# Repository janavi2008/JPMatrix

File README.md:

# JPMatrix
a scalable led matrix display where 'tiles' can connect to each other in a row to allow for any size display. each tile has a 8x8 matrix. it runs on a rapberry pi pico that has to be connected externally, with shift registers for multiplexing, and a logic level shifter ic to convert the 3.3v pico outputs to 5v for the shift register inputs.
im writing the firmware to display conways game of life, because i think itd look super cool.

# How it works
multiplexing is a way to control a bunch of leds using fewer pins on the microcontroller. basically, instead of connecting each led to its own output pin, the leds are arranged in a matrix, and all anodes in one column are tied together, and the cathodes in one row are tied together. each row and column is connected to a microcontroller pin. the microcontroller passes current through one row at a time and simultaneously connecting the columns with whichever leds are supposed to be on for that row. it cycles through the rows super fast, way faster for the human eye to comprehend, so it looks as if the leds are all lit up at the same time, when in reality, only one row is on at a time- this is known as persitance of vision. however, this still would use one output pin for each row and column (so 16 per tile) and thats not feasable, which is why im using shift registers.
shift registers let you transmit the data serially over one data line rather than one for each row and column, drastically saving the pin count. it used 4 pins - data, latch, clock, and oe(output enable). the data pin sends the data to the shift registers, the clock pin handles the timing(when to read the data pin), latch saves the data once its been loaded, and the oe manages when the data is outputted to the leds. multiple shift registers can be used by daisy chaining without needing more pins - each chip has a data in and a data out, so the data out from one chip can connect to the data in to another. im using one shift register for columns, and one for the rows. the one for the rows is a power shift register, with internal mosfets on each line, so it can handle higher currents.

# Design
i desinged a pcb, using IC 74HCT595 as a shift register, TPIC6C595 as a power shift register, 74HCT125 for logic level shifting, 64 LEDs, and input header pins to connect to the previous tile or the raspberry pi and output header pins to connect to the next tile. i also put in some resistors and decoupling capacitors.

# BOM

| Item | Qty | Supplier | Total Cost |
| :--- | :---: | :--- | ---: |
| raspberry pi pico | 1 | robu | $4.05 |
| TPIC6C595 | 2 | robu | $3.10 |
| 74HCT595 | 2 | robu | $1.00 |
| 74HCT125 | 2 | robu | $0.78 |
| 0805 smd LED | 128 | robu | $1.4 |
| 0603 smd 0.1uf capacitor | 6 | robu | $0.15 |
| 0603 smd 100uf electrolytic capacitor | 2 | robu | $0.22 |
| 0603 330 ohm resistor | 16 | robu | $0.15 |
| 0603 10k resistor | 2 | robu | $0.15 |
| 0603 100 ohm resistor | 2 | robu | $0.15 |
| male header pins | 16 | robu | $0.2 |
| pcb manufacture | 5 | zbotic | $10.00 |

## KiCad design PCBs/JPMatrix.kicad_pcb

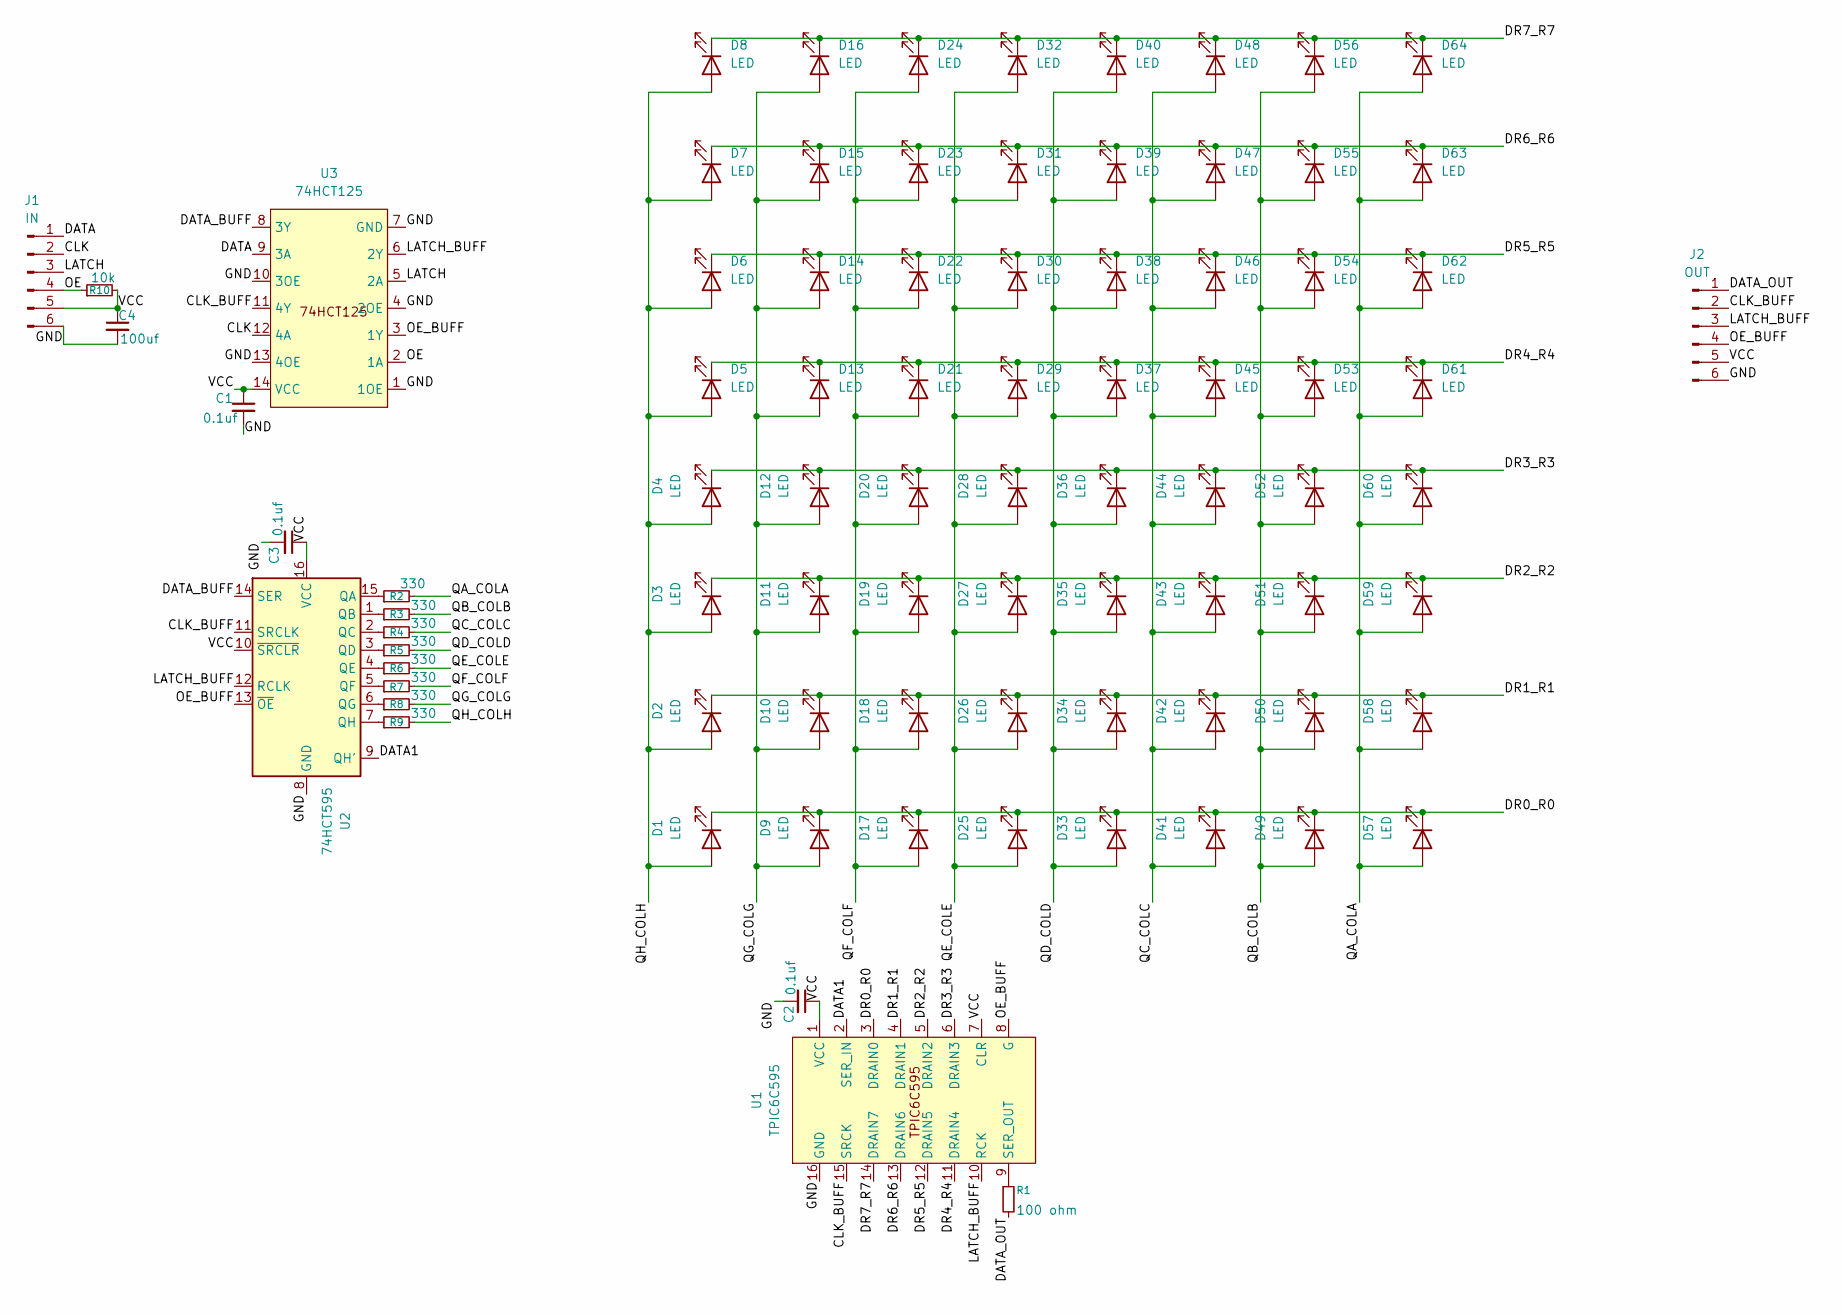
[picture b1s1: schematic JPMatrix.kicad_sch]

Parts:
C1, C2, C3: 0.1uf; C_0603_1608Metric_Pad1.08x0.95mm_HandSolder
C4: 100uf; CP_Elec_6.3x5.9
D1, D2, D3, D4, D5, D6, D7, D8, D9, D10, D11, D12, D13, D14, D15, D16, D17, D18, D19, D20, D21, D22, D23, D24, D25, D26, D27, D28, D29, D30, D31, D32, D33, D34, D35, D36, D37, D38, D39, D40, D41, D42, D43, D44, D45, D46, D47, D48, D49, D50, D51, D52, D53, D54, D55, D56, D57, D58, D59, D60, D61, D62, D63, D64: LED; LED_0805_2012Metric_Pad1.15x1.40mm_HandSolder
J1: IN; PinHeader_1x06_P2.54mm_Vertical
J2: OUT; PinHeader_1x06_P2.54mm_Vertical
R1: 100 ohm; R_0603_1608Metric_Pad0.98x0.95mm_HandSolder
R2, R3, R4, R5, R6, R7, R8, R9: 330; R_0603_1608Metric_Pad0.98x0.95mm_HandSolder
R10: 10k; R_0603_1608Metric_Pad0.98x0.95mm_HandSolder
U1: TPIC6C595; SOIC-16_3.9x9.9mm_P1.27mm
U2: 74HCT595; SOIC-16_3.9x9.9mm_P1.27mm
U3: 74HCT125; TSSOP-14_4.4x5mm_P0.65mm

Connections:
/CLK: J1.2, U3.12 (4A)
/CLK_BUFF: J2.2, U1.15 (SRCK), U2.11 (SRCLK), U3.11 (4Y)
/DATA: J1.1, U3.9 (3A)
/DATA1: U1.2 (SER_IN), U2.9 (QH')
/DATA_BUFF: U2.14 (SER), U3.8 (3Y)
/DATA_OUT: J2.1, R1.2
/DR0_R0: D1.1 (K), D9.1 (K), D17.1 (K), D25.1 (K), D33.1 (K), D41.1 (K), D49.1 (K), D57.1 (K), U1.3 (DRAIN0)
/DR1_R1: D2.1 (K), D10.1 (K), D18.1 (K), D26.1 (K), D34.1 (K), D42.1 (K), D50.1 (K), D58.1 (K), U1.4 (DRAIN1)
/DR2_R2: D3.1 (K), D11.1 (K), D19.1 (K), D27.1 (K), D35.1 (K), D43.1 (K), D51.1 (K), D59.1 (K), U1.5 (DRAIN2)
/DR3_R3: D4.1 (K), D12.1 (K), D20.1 (K), D28.1 (K), D36.1 (K), D44.1 (K), D52.1 (K), D60.1 (K), U1.6 (DRAIN3)
/DR4_R4: D5.1 (K), D13.1 (K), D21.1 (K), D29.1 (K), D37.1 (K), D45.1 (K), D53.1 (K), D61.1 (K), U1.11 (DRAIN4)
/DR5_R5: D6.1 (K), D14.1 (K), D22.1 (K), D30.1 (K), D38.1 (K), D46.1 (K), D54.1 (K), D62.1 (K), U1.12 (DRAIN5)
/DR6_R6: D7.1 (K), D15.1 (K), D23.1 (K), D31.1 (K), D39.1 (K), D47.1 (K), D55.1 (K), D63.1 (K), U1.13 (DRAIN6)
/DR7_R7: D8.1 (K), D16.1 (K), D24.1 (K), D32.1 (K), D40.1 (K), D48.1 (K), D56.1 (K), D64.1 (K), U1.14 (DRAIN7)
/GND: C1.2, C2.2, C3.2, C4.2, J1.6, J2.6, U1.16 (GND), U2.8 (GND), U3.1 (1OE), U3.4 (2OE), U3.7 (GND), U3.10 (3OE), U3.13 (4OE)
/LATCH: J1.3, U3.5 (2A)
/LATCH_BUFF: J2.3, U1.10 (RCK), U2.12 (RCLK), U3.6 (2Y)
/OE: J1.4, R10.1, U3.2 (1A)
/OE_BUFF: J2.4, U1.8 (G), U2.13 (~OE), U3.3 (1Y)
/QA_COLA: D57.2 (A), D58.2 (A), D59.2 (A), D60.2 (A), D61.2 (A), D62.2 (A), D63.2 (A), D64.2 (A), R2.2
/QB_COLB: D49.2 (A), D50.2 (A), D51.2 (A), D52.2 (A), D53.2 (A), D54.2 (A), D55.2 (A), D56.2 (A), R3.2
/QC_COLC: D41.2 (A), D42.2 (A), D43.2 (A), D44.2 (A), D45.2 (A), D46.2 (A), D47.2 (A), D48.2 (A), R4.2
/QD_COLD: D33.2 (A), D34.2 (A), D35.2 (A), D36.2 (A), D37.2 (A), D38.2 (A), D39.2 (A), D40.2 (A), R5.2
/QE_COLE: D25.2 (A), D26.2 (A), D27.2 (A), D28.2 (A), D29.2 (A), D30.2 (A), D31.2 (A), D32.2 (A), R6.2
/QF_COLF: D17.2 (A), D18.2 (A), D19.2 (A), D20.2 (A), D21.2 (A), D22.2 (A), D23.2 (A), D24.2 (A), R7.2
/QG_COLG: D9.2 (A), D10.2 (A), D11.2 (A), D12.2 (A), D13.2 (A), D14.2 (A), D15.2 (A), D16.2 (A), R8.2
/QH_COLH: D1.2 (A), D2.2 (A), D3.2 (A), D4.2 (A), D5.2 (A), D6.2 (A), D7.2 (A), D8.2 (A), R9.2
/VCC: C1.1, C2.1, C3.1, C4.1, J1.5, J2.5, R10.2, U1.1 (VCC), U1.7 (CLR), U2.10 (~SRCLR), U2.16 (VCC), U3.14 (VCC)
unnamed: R1.1, U1.9 (SER_OUT)
unnamed: R2.1, U2.15 (QA)
unnamed: R3.1, U2.1 (QB)
unnamed: R4.1, U2.2 (QC)
unnamed: R5.1, U2.3 (QD)
unnamed: R6.1, U2.4 (QE)
unnamed: R7.1, U2.5 (QF)
unnamed: R8.1, U2.6 (QG)
unnamed: R9.1, U2.7 (QH)

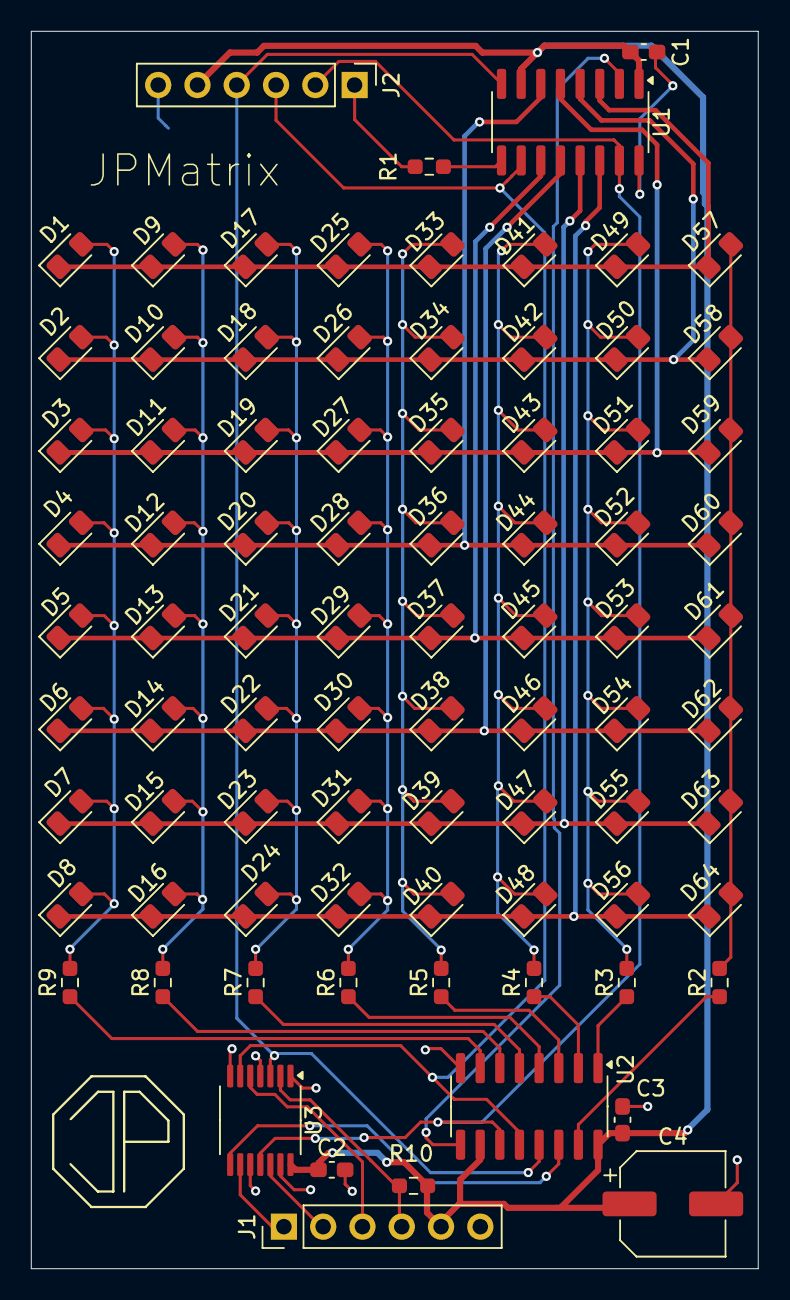
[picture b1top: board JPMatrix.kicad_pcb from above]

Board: 2 copper layers, 47.0 x 80.0 mm, 83 parts (0 on the bottom side), 37 nets.
